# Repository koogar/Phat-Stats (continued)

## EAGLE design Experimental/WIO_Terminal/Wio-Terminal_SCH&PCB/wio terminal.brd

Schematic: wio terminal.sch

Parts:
ANT2: 2.4G+5G; ANT2P-AMEBA-D-MODULE
BUZ1: LET5020CS-03L-4.0-12-R; BZ3-SMD-5.0X5.0X2.5MM
C1, C6: 22uF; C0603
C2, C3: 10uF; C0603
C4: 10uF/10V; C0603
C5, C7, C8, C10, C11, C14, C15, C29, C30, C31, C32, C33, C35, C36, C39, C48: 100nF; C0402
C9, C16, C34, C37, C41, C53, C54, C55: 1uF; C0402
C12, C13, C42, C43: 10pF; C0402
C27, C28: DNP; C0402
C38, C40, C60, C61, C62, C64, C65, C66, C67: 10uF; C0402
C49, C50: 22pF; C0402
C51, C52: 12pF; C0402
C63: 22uF/10V; AVX-A
D1, D6, D8: ESD9B3.3ST5G; ESD-0402
D2, D3, D4: CESDP0402UC5VB; ESD-0402
D5, D9: B5819WS; SOD-323
D7: Blue 90D; LED-SIDE-VIEW-0603-RIGHT
D10: IR; LED-0603
D15: SP3012-06UTG; UDFN14-0.5-3.5X1.35X0.5MM
F1: 1206L300SLTHYR; F1206
FB2, FB3: 120R/2A; F0402
J1: ST-TF-003J; MICRO-SD9+4P-SMD-16.1X14.5X1.85MM
J2: DL; H5-SMD-2.0-TEST
J3: FPC-CONNECTOR-10PTOP''; FPC10-SMD-0.5-10.6X3.5X4.5MM
J4, J5: SMD_GROVE; HW4-SMD-2.0-90D
J6: XW05200-20; FPC20-SMD-0.5-90D
J7: SMD_Header; H6-SMD-2.0_TEST
K1, K2, K3: BUTTON-2+2P-TS-1073B; SW2+2P-3.45-4.8X2.5X1.8MM
L2: 2.2uH; L0805
L3: 0.5pF; L0402
L5: SPH252012H1R2MT; L2520
L6: CBC3225T100MR; L2520
LED1: Green 90D; LED-SIDE-VIEW-0603-RIGHT
MIC1: B4013AM422-042; MIC2-SMD-4X4MM
Q1, Q3, Q4, Q13, Q16: 2N7002,215; SOT-23
Q2, Q7, Q8, Q9, Q10, Q12, Q14, Q15: CJ3407; SOT-23
Q11: BC856S; SOT-363
R1, R2: 5.1K; R0402
R3, R4, R13, R14, R20, R38, R48, R49, R54, R61, R62, R63: 4.7K; R0402
R5, R8, R12, R17, R21, R39, R40, R41, R42, R46, R53, R66, R67, R68, R69, R72, R79, R81, R82, R83: 0R; R0402
R6, R35, R43, R44, R45, R57, R74, R75, R76: 33R; R0402
R7, R16, R18, R19, R23, R24, R36, R37, R84, R85, R86, R87, R91, R95, R100: 100K; R0402
R9, R22, R26, R27, R77, R94, R96, R97, R98: 10K; R0402
R10, R32, R33, R34, R50, R58, R59, R60, R64, R65, R73, R90, R93, R102, R103: DNP; R0402
R11: 4.7k; R0402
R25, R28, R31, R88, R99: 1K; R0402
R29, R52, R78, R80: 100k; R0402
R30: 330R; R0402
R47, R51: 1k; R0402
R55, R56: 22R; R0402
R70: 150K; R0402
R71: 33K; R0402
SW1: DHT-1500; SWITCH-2X3P
SW3: MK-13E03N-G; SW4-SMD-11.2X3.6MM
U1: ATSAMD51P19A; TFBGA120-0.5-8X8MM
U2: LMV358IDGKR; MSOP8-0.65-3X3MM
U3: RPI; H2X20-SMD-2.54-50.8X5MM-LONG
U4: LCD; LCM18-0.8-60.26X42.72X2.2MM
U5: LIS3DHTR; LGA16-0.5-3X3MM
U8: SENSOR-PD15-22C/TR8; SNR4-SMD-3.2X2.7MM
U9: SN74LVC1G125DCKR; SC-70-5
U10: RTL8720D; MODULE-32P-0.8-13X12MM-MOTHER
U11: ATECC608; UDFN8-0.5-2X3X0.5MM
U12: MP2161GJ; TSOT23-8
U13: AP2112K-3.3TRG1; SOT-23-5
U14: W25Q32JVZPIM; SOIC8-1.27-5.3X5.3MM
USB1: USB_TYPE C; USB2.0-TYPE-C
X2: 32.768KHz FC-12M; X2-SMD-L2.0X1.2X0.55MM
X4: 32MHz / 306010026; X4-SMD-3.2X2.5X0.7MM

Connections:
3V3_OUTPUT_CTR: R99.2, U1.P12 (PC15/I15/SERCOM7+6.3/TCC0.5+1.1)
5V_OUTPUT_CTR: R88.1, U1.R11 (PC14/I14/SERCOM7+6.2/TCC0.4+1.0)
A0/D0: J5.1, U1.J2 (PB08/I8/AIN0.2+1.0/SERCOM4.0/TC4.0/PTC), U3.13 (GPIO27/GEN2)
A1/D1: J5.2, U1.K1 (PB09/I9/AIN0.3+1.1/SERCOM4.1/TC4.0/PTC), U3.15 (GPIO22/GEN3)
A2/D2: U1.M1 (PA07/I7/AIN0.7/SERCOM0.1/TC1.1/PTC), U3.16 (GEN4/GPIO23)
A3/D3: U1.F1 (PB04/I4/AIN1.6/PTC), U3.18 (GEN5/GPIO24)
A4/D4: U1.G1 (PB05/I5/AIN1/7/PTC), U3.22 (GEN6/GPIO25)
A5/D5: U1.H2 (PB06/I6/AIN1.8/PTC), U3.32 (GPIO12)
A6/D6: U1.K2 (PA04/I4/VREFB/AIN0.4/SERCOM0.1/TC0.0/PTC), U3.33 (GPIO13)
A7/D7: U1.J1 (PB07/I7/AIN1.9/PTC), U3.36 (GPIO16)
A8/D8: U1.L2 (PA06/I6/VREFC/AIN0.6/SERCOM0.1/TC1.0/PTC), U3.37 (GPIO26)
BUTTON1: K1.2, R49.1, U1.A10 (PC26/I10/TRACEDATA.1)
BUTTON2: K2.2, R3.1, U1.A9 (PC27/I11/SERCOM1.0/TRACECLK)
BUTTON3: K3.2, R4.1, U1.B9 (PC28/I12/SERCOM1.1/TRACEDATA.0)
BUZZER_CTR: R5.1, U1.P9 (PD11/I6/SERCOM7+6.3/TCC0.4)
DAC0: U1.E1 (PA02/I2/AIN0.0/VOUT0), U3.11 (GPIO17/GEN0)
DAC1: U1.L1 (PA05/I5/AIN0.5/VOUT1/SERCOM0.2/TC0.1), U3.26 (!CE!/GPIO7)
DN: D3.1, R55.1, USB1.A7 (A7/DN1), USB1.B7 (B7/DN2)
DP: D4.1, R56.2, USB1.A6 (A6/DP1), USB1.B6 (B6/DP2)
FPC_D3/PWM3: J6.4, U1.A12 (PB28/I14/SEROM2+4.2/TCC1.4/I2SSCK.1)
FPC_D4/PWM4: J6.5, U1.G15 (PB17/SERCOM5.1/I2SMCK0/TC6.1+TCC3.1+0.5)
FPC_D5/PWM5: J6.6, U1.B11 (PB29/I15/SERCOM2+4.3/TCC1.5/I2SMCK.1)
FPC_D6/PWM6: J6.7, U1.R13 (PA14/I14/SERCOM2+4.2/TC3.0+TCC2.0+1.2)
FPC_D7/A7: J6.8, U1.C2 (PC01/I1/ADC1.11)
FPC_D8/A8: J6.9, U1.D1 (PC02/I2/ADC1.4)
FPC_D9/A9: J6.10, U1.E2 (PC03/I3/ADC1.5)
FPC_D10/PWM10: J6.11, U1.N1 (PC04/I4/SERCOM6.0/TCC0.0)
FPC_D11/A11: J6.12, U1.B4 (PC31/I15/AIN1.13)
FPC_D12/A12: J6.13, U1.G2 (PD00/I0/AIN1.14)
FPC_D13/A13: R79.2, U1.H1 (PD01/I1/AIN1.14)
GND: ANT2.1, C1.1, C2.1, C3.1, C4.1, C5.1, C6.1, C7.2, C8.2, C9.2, C10.2, C11.1, C12.2, C13.2, C14.1, C15.2, C16.2, C27.1, C28.1, C29.1, C30.1, C31.1, C32.2, C33.2, C35.2, C36.2, C37.2, C38.2, C39.2, C40.2, C41.2, C42.2, C43.2, C48.2, C49.1, C50.1, C51.2, C52.2, C53.2, C54.2, C60.2, C61.2, C62.2, C63.-, C64.1, C65.1, C66.1, C67.1, D1.1, D2.2, D3.2, D4.2, D6.1, D8.1, D15.5 (10), D15.10, J1.6 (VSS), J1.G1, J1.G2, J1.G3, J1.G4 (G3), J2.2, J3.6, J3.P1, J3.P2, J4.4, J5.4, J6.17, J6.18, J6.P1, J6.P2, J7.5, K1.1, K1.3 (S1), K1.4 (S2), K2.1, K2.3 (S1), K2.4 (S2), K3.1, K3.3 (S1), K3.4 (S2), LED1.2 (-), MIC1.2 (-), MIC1.3 (-), MIC1.4 (-), MIC1.5 (-), Q1.2 (S), Q3.2 (S), Q4.2 (S), Q13.2 (S), Q16.2 (S), R1.1, R2.1, R7.1, R16.2, R19.2, R23.2, R25.1, R28.1, R50.2, R52.1, R54.2, R72.1, R77.1, R78.1, R80.2, R91.2, R93.1, R95.1, R97.1, R98.1, R100.1, SW1.5, SW1.7, SW1.8, SW3.3, U1.D2 (GNDIO0), U1.F6 (GNDIO7), U1.F9 (GNDIO6), U1.G10 (GNDIO5), U1.H6 (GNDANA0), U1.J6 (GNDIO1), U1.J10 (GNDIO4), U1.K8 (GNDIO2)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
GPCLK0: U1.R5 (PB14/I14/SERCOM4.2/PCC8/TC5.0+TCC4.0+0.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), U3.7 (GPIO4/GCKL)
GPCLK1: U1.R4 (PB12/I12/SERCOM4.0/I2SCK1/TC4.0+TCC3.0+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), U3.29 (GPIO5)
GPCLK2: U1.P6 (PB13/I13/SERCOM4.1/I2SMCK1/TC4.1+TCC3.1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), U3.31 (GPIO6)
GYROSCOPE_INT1: U1.K14 (PC21/I5/TCC0.5/SDHC1.SDWP), U5.11 (INT1)
I2C0_SCL: R13.2, U1.R12 (PA12/I12/I2C/SERCOM2.0+4.1/TC2.0+TCC0.7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), U3.28 (ID_SC), U5.4 (SCL/SPC), U11.6 (SCL)
I2C0_SDA: R14.2, U1.P13 (PA13/I13/I2C/SERCOM2.1+4.0/TC2.1+TCC0.7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), U3.27 (ID_SD), U5.6 (SDA/SDI/SDO), U11.5 (SDA)
I2C1_SCL: J4.1, R33.1, U1.R15 (PA16/I2C/I0/SERCOM1.0+3.1/TC2.0+TCC1.0+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), U3.5 (GPIO3/SCL1)
I2C1_SDA: J4.2, R34.1, U1.P14 (PA17/I2C/I1/SERCOM1.1+3.0/TC2.1+TCC1.1+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), U3.3 (GPIO2/SDA1)
I2S_BLCK: U1.H15 (PB16/I0/SERCOM5.0/I2SCK0/TC6.0+TCC3.0+0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), U3.12 (GPIO18)
I2S_LRCLK: U1.E14 (PA20/I4/SERCOM3+5.2/I2SFS0/TC7.0+TCC1.4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), U3.35 (GPIO19)
I2S_SDIN: U1.D15 (PA21/I5/SERCOM3+5.3/I2SDO/TC7.1+TCC1.5+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), U3.38 (GPIO20)
I2S_SDOUT: U1.D14 (PA22/I2C/16/SERCOM3.0+5.1/I2SDI/TC4.0+T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), U3.40 (GPIO21)
IRQ0: R103.1, U1.L15 (PC20/I4/TCC0.4/SDHC1.SDCD), U10.2
IR_CTL: R47.2, U1.B5 (PB31/I15/SERCOM5.0/TC0.1+TCC4.1+0.7)
LCDVCC_3V3: C29.2, C30.2, C31.2, FB2.2, R48.2, U4.9 (VCC), U4.10 (LEDA)
LCD_BACKLIGHT_CTR: R17.2, U1.N2 (PC05/I5/SERCOM6.0)
LCD_CS: R74.2, U1.E15 (PB21/SERCOM3.1+7.0/TCC1.3)
LCD_D/C: R57.2, U1.P1 (PC06/I6/SERCOM6.2/SDHC0.SDCD)
LCD_MISO: R76.2, U1.G14 (PB18/I2/SERCOM5+7.2/TCC1.0+QDI.0)
LCD_MOSI: R75.2, U1.F15 (PB19/I3/SERCOM5+7.3/CC1.1/QDI.1)
LCD_RESET: R48.1, U1.P2 (PC07/I9/SERCOM6.3/SDHC0.SDWP), U4.2 (RESET)
LCD_SCK: R35.2, U1.F14 (PB20/I4/SERCOM3.0+7.1/TCC1.2/QDI.2)
LCD_XL: R39.1, U1.P10 (PC10/I10/SERCOM6.2+7.2/TCC0.0+1.4)
LCD_XR: R41.1, U1.R10 (PC12/I12/SERCOM7.0+6.1/TCC0.2+1.6)
LCD_YD: R42.1, U1.P11 (PC13/I13/SERCOM7.1+6.0/TCC0.3+1.7)
LCD_YU: R40.1, U1.R9 (PC11/I11/SERCOM6+7.3/TCC0.1+1.5)
MCU_FLASH_QSPI_CLK: U1.R3 (PB10/I10/SERCOM4.2/I2SDI/TC5.0+TCC0.4+1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), U14.6 (CLK)
MCU_FLASH_QSPI_CS: R32.1, U1.P5 (PB11/I11/SERCOM4.3/I2SFS1/TC5.1+TCC0.5+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), U14.1 (/CS)
MCU_FLASH_QSPI_IO0: U1.R1 (PA08/I2C/AIN0.8+1.2/SERCOM0.0+2.1/I2SMC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), U14.5 (DIO)
MCU_FLASH_QSPI_IO1: U1.P3 (PA09/I2C/I9/AIN0.9+1.3/SERCOM0.1+2.0/I2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), U14.2 (DO)
MCU_FLASH_QSPI_IO2: R58.1, U1.R2 (PA10/I10/AIN0.10/SERCOM0+2.2/I2SCK1/TC1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), U14.3 (/WP)
MCU_FLASH_QSPI_IO3: R59.1, U1.P4 (PA11/I11/AIN0.11/SERCOM0+2.3/I2SDO/TC1.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), U14.7 (/HOLD)
MCU_RESET: D6.2, J3.4, J7.4, R30.2, SW3.1, U1.A8 (!RESET)
MIC_OUTPUT: C55.2, U1.A4 (PC30/I14/AIN1.12)
unnamed: L6.1, U1.A6 (VSW)
unnamed: R12.2, U1.F2 (PA03/I3/VREFA/AIN0.1)
unnamed: D2.1, F1.1, USB1.A4_B9 (A4/B9/VBUS), USB1.B4_A9 (B4/A9/VBUS)
unnamed: R1.2, USB1.A5 (A5/CC1)
unnamed: R2.2, USB1.B5 (B5/CC2)
unnamed: Q4.3 (D), R6.2
unnamed: BUZ1.-, D5.+, R6.1
unnamed: Q4.1 (G), R5.2, R7.2
unnamed: C12.1, R35.1, U4.3 (SCL)
unnamed: ANT2.2, C28.2, L3.1
unnamed: R69.1, U1.K15 (PC22/I6/SERCOM1.0+3.1/TCC0.6)
unnamed: R68.1, U1.J14 (PC23/I7/SERCOM1.1+3.0/TCC0.7)
unnamed: Q7.1 (G), Q8.3 (D), R91.1, SW3.2
unnamed: C13.1, R57.1, U4.4 (D/C)
unnamed: R65.2, U10.23
unnamed: R74.1, U4.5 (CS)
unnamed: C43.1, R75.1, U4.6 (SDA)
unnamed: R10.2, U10.22
unnamed: Q13.3 (D), R83.2
unnamed: Q13.1 (G), R47.1, R80.1
unnamed: C42.1, R76.1, U4.7 (SDO)
unnamed: Q9.1 (G), Q14.1 (G), Q16.3 (D), R93.2, R94.1
unnamed: R66.1, U10.7
unnamed: R67.1, U10.10
unnamed: R46.1, U4.11 (LEDK), U4.12 (LEDK), U4.13 (LEDK), U4.14 (LEDK)
unnamed: Q2.1 (G), R19.1, R20.2, U9.4 (Y)
unnamed: Q1.1 (G), R16.1, R17.1
unnamed: C34.2, R23.1, R24.2
unnamed: R18.2, R21.1, U9.1 (!OE!), U9.2 (A)
unnamed: LED1.1 (+), R31.2
unnamed: R24.1, U2.3 (+IN1)
unnamed: C4.2, C5.2, F1.2, Q2.3 (D)
unnamed: C34.1, MIC1.1 (+), R22.2
unnamed: R25.2, R26.1, U2.2 (-IN1)
unnamed: R26.2, U2.1 (OUT1), U2.5 (+IN2)
unnamed: R27.1, R28.2, U2.6 (-IN2)
unnamed: C50.2, U1.B1 (PA01/I1/SERCOM1.1/TC2.1), X2.1
unnamed: C36.1, C37.1, C38.1, L6.2, U1.A7 (VDDCORE)
unnamed: R39.2, U4.15 (XL)
unnamed: C49.2, U1.A1 (PA00/I0/SERCOM1.0/TC2.0), X2.2
unnamed: C35.1, R9.1, R30.1
unnamed: R40.2, U4.16 (YU)
unnamed: Q11.2 (B), Q11.5 (B), Q11.6 (C), R98.2
unnamed: R41.2, U4.17 (XR)
unnamed: R42.2, U4.18 (YD)
unnamed: R81.1, U10.9
unnamed: Q1.3 (D), R46.2
unnamed: R82.1, U10.8
unnamed: R77.2, R79.1, U8.2-1 (2), U8.2-2 (2)
unnamed: Q10.1 (G), Q11.3 (C), R97.2
unnamed: D10.-, R83.1
unnamed: Q8.1 (G), R29.1, SW3.4
unnamed: Q9.3 (D), Q14.3 (D)
unnamed: C52.1, R8.2, X4.1 (X1)
unnamed: R50.1, U1.C1 (PC00/I1/ADC1.10)
unnamed: D7.2 (-), Q3.3 (D)
unnamed: D7.1 (+), R51.2
unnamed: Q3.1 (G), R52.2, R53.2
unnamed: D15.1 (14), D15.14, J1.8 (DATA1), R60.1
unnamed: Q12.3 (D), Q15.3 (D)
unnamed: Q16.1 (G), R88.2, R100.2
unnamed: C55.1, R27.2, U2.7 (OUT2)
unnamed: Q12.1 (G), Q15.1 (G), R95.2, R96.1, R99.1
unnamed: L5.1, U12.3 (SW)
unnamed: D15.7 (8), D15.8, J1.1 (DATA2), R64.1
unnamed: R71.1, R72.2
unnamed: C27.2, L3.2, U10.31
unnamed: R70.1, R71.2, U12.7 (FB)
unnamed: D15.2 (13), D15.13, J1.7 (DO), R43.1
unnamed: D15.3 (12), D15.12, J1.5 (SCLK), R44.1
unnamed: D15.4 (11), D15.11, J1.3 (DI), R45.1
PWR_EN: Q7.3 (D), R73.1, R78.2, R90.2, U12.8 (EN), U13.3 (!SHUTDOWN)
RPI_3V3: Q10.3 (D), Q11.1 (E), Q15.2 (S), U3.1 (3V3), U3.17 (3V3)
RPI_5V: D9.+, Q14.2 (S), R20.1, U3.2 (5V0), U3.4 (5V0)
RTL8720D_CHIP_PU: C9.1, J2.5, J3.10, R11.1, U1.P15 (PA18/I2/SERCOM1+3.2/TC3.0+TCC1.2+0.6/PTC), U10.24
RTL8720D_HSPI_CLK: R10.1, R66.2, U1.B13 (PB25/SERCOM0.1+2.0/QDI.2)
RTL8720D_HSPI_CS: R82.2, U1.B10 (PC25/I9/SERCOM0+2.3/TRACEDATA.2)
RTL8720D_HSPI_MISO: R81.2, U1.A11 (PC24/I8/SERCOM0+2.2/TRACEDATA.3)
RTL8720D_HSPI_MOSI: R65.1, R67.2, U1.B14 (PB24/I8/SERCOM0.0+2.1/QDI.1)
RTL8720D_RXD: J2.4, J3.9, R69.2, U10.26
RTL8720D_TXD: J2.3, J3.8, R68.2, U10.25
RXD: U1.B12 (PB27/I13/SERCOM2.1+4.0/TCC1.3), U3.10 (RXD0/GPIO15)
SD_CS: D15.6 (9), D15.9, J1.2 (CS), R63.1, U1.L14 (PC19/I3/SERCOM6+0.3/TCC0.3)
SD_DET: D8.2, J1.9 (CDN), R36.1, U1.H14 (PD21/I11/SERCOM1+3.3/TCC1.1/SDHC1.SDWP)
SD_MISO: R43.2, R61.1, U1.M15 (PC18/I2/SERCOM6.2+0.2/TCC0.2/QDI.2)
SD_MOSI: R45.2, R62.1, U1.N15 (PC16/I0/SERCOM6.0+0.1/TCC0/QDI.0)
SD_SCK: R44.2, U1.M14 (PC17/I1/SERCOM6.1+0.0/TCC0.1/QDI.1)
SPI_CS: U1.B3 (PB01/I1/AIN0.13/SERCOM5.3/TC7.1/PTC), U3.24 (!CE0!/GPIO8)
SPI_MISO: J6.2, U1.A3 (PB00/I0/AIN0.12/SERCOM5.2/TC7.0/PTC), U3.21 (GPIO9/MISO)
SPI_MOSI: J6.1, U1.A2 (PB02/I2/AIN0.14/SERCOM5.0/TC6.0+TCC2.2/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), U3.19 (GPIO10/MOSI)
SPI_SCK: J6.3, U1.B2 (PB03/I3/AIN0.15/SERCOM5.1/TC6.1/PTC), U3.23 (GPIO11/SCLK)
SWDCLK: J3.1, J7.1, R33.2, R38.2, U1.B7 (PA30/I14/SERCOM1.2/SWCLK)
SWDIO: J3.2, J7.2, R34.2, R54.1, U1.B6 (PA31/I15/SERCOM1.3/SWDIO)
SWITCH_B: R86.1, SW1.4, U1.R8 (PD12/I7/TCC0.5)
SWITCH_U: R87.1, SW1.6, U1.J15 (PD20/I10/SERCOM1+3.2/TCC1.0/SDHC1.SDCD)
SWITCH_X: R37.1, SW1.1, U1.R6 (PD08/I3/SERCOM7.0+6.1/TCC0.1)
SWITCH_Y: R85.1, SW1.3, U1.P8 (PD09/I4/SERCOM7.1+6.0/TCC0.2)
SWITCH_Z: R84.1, SW1.2, U1.R7 (PD10/I5/SERCOM7+6.2/TCC0.3)
SWO: J3.3, J7.3, U1.A5 (PB30/I14/SERCOM5.1/TC0.0+TCC4.0+0.6/SWO)
SYNC: R102.1, U1.N14 (PA19/I3/SERCOM1+3.3/TC3.1+TCC1.3+0.7/PT), U10.3
TXD: U1.A13 (PB26/I12/SERCOM2.0+4.1/TCC1.3), U3.8 (TXD0/GPIO14)
USB_5V: C3.2, C8.1, C66.2, C67.2, D9.-, J6.19, J6.20, Q2.2 (S), Q7.2 (S), Q8.2 (S), Q9.2 (S), R29.2, R73.2, R90.1, R94.2, U12.2 (VIN), U13.1 (VIN)
USB_D+: R56.1, U1.B15 (PA25/19/SERCOM3+5.3/D+)
USB_D-: R55.2, U1.C15 (PA24/I8/SERCOM3+5.2/D-)
USB_HOST_EN: R21.2, U1.B8 (PA27/I11)
USER_LED: R53.1, U1.R14 (PA15/I15/SERCOM2+4.3/TC3.1+TCC2.1+1.3)
VCC3V3_8720: C1.2, C2.2, C6.2, C7.1, C10.1, J2.1, R11.2, R102.2, R103.2, U10.16, U13.5 (VOUT)
VCC3V3_MCU_A: C33.1, C60.1, L2.1, R12.1, R22.1, U1.G6 (VDDANA0), U1.M2 (VDDANA1), U2.8 (+V)
VCC3V3_MCU_D: C15.1, C16.1, C39.1, C40.1, C41.1, C48.1, C62.1, D1.2, FB3.2, J1.4 (VDD), J7.6, R3.2, R4.2, R9.2, R32.2, R36.2, R37.2, R38.1, R49.2, R51.1, R58.2, R59.2, R60.2, R61.2, R62.2, R63.2, R64.2, R84.2, R85.2, R86.2, R87.2, U1.F7 (VDDIO7), U1.F8 (VDDIO6), U1.F10 (VDDIO5), U1.H10 (VDDIO4), U1.K6 (VDDIOB1), U1.K7 (VDDIOB2), U1.K10 (VDDIO3), U14.8 (VCC)
VCC_3V3: BUZ1.+, C11.2, C14.2, C32.1, C53.1, C54.1, C61.1, C63.+, C64.2, C65.2, D5.-, D10.+, FB2.1, FB3.1, J4.3, J5.3, J6.15, J6.16, L2.2, L5.2, Q10.2 (S), Q11.4 (E), Q12.2 (S), R13.1, R14.1, R18.1, R31.1, R70.2, R96.2, U5.1 (VDD_IO), U5.8 (CS), U5.14 (VDD), U8.1-1 (1), U8.1-2 (1), U9.5 (VCC), U11.8 (VCC), U12.5 (OUT)
XIN: R8.1, U1.A15 (PB22/I6/SERCOM1+5.2/TC7.0/QDI.2)
XOUT: C51.1, U1.A14 (PB23/I7/SERCOM1+5.3/TC7.1/QDI.0), X4.3 (X2)

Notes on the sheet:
First version
20190812
Milo
Power
ATSAMD51P19A
Buzzer & MIC
WIFI+BLE
Gyroscope & LCD
8720 module Download
Replace with 0R resistance
USB HOST selection Power selection
Close to USB TYPE C
Close to ATSAMD51P19A power Pin
Header Interface and Button
Input current:2A
Output current:2A
Input current 500mA
Input current 600mA
ATSAMD51P19A Download
I2C Address 0x19
To guarantee the XOSC32K behavior in crystal mode,PC00 must be static
MCU Reset
Power ON
Power OFF
PA28/CTS/PWM6/RREF
PB17/SPI_DATA1
PB16/SPI_CS
PB13/SPI_CLK
PB14/SPI_DATA0
ADC6
ADC4/TXD
ADC5/RXD/I2C_SDA
PA25/RXD/USB_DM/I2C_SCL
PA26/TXD/USB_DP
PA30/PWM7/SWD_CLK
PA27/RTS/SWD_DATA
PB20/TXD/PWM12/I2S_CLK/SPI_DATA0/I2C_SCL
PB21/RXD/PWM13/I2S_WS/SPI_CLK/I2C_SDA
PA15/CTS/CS
PA14/RTS/CLK/I2S_TX2

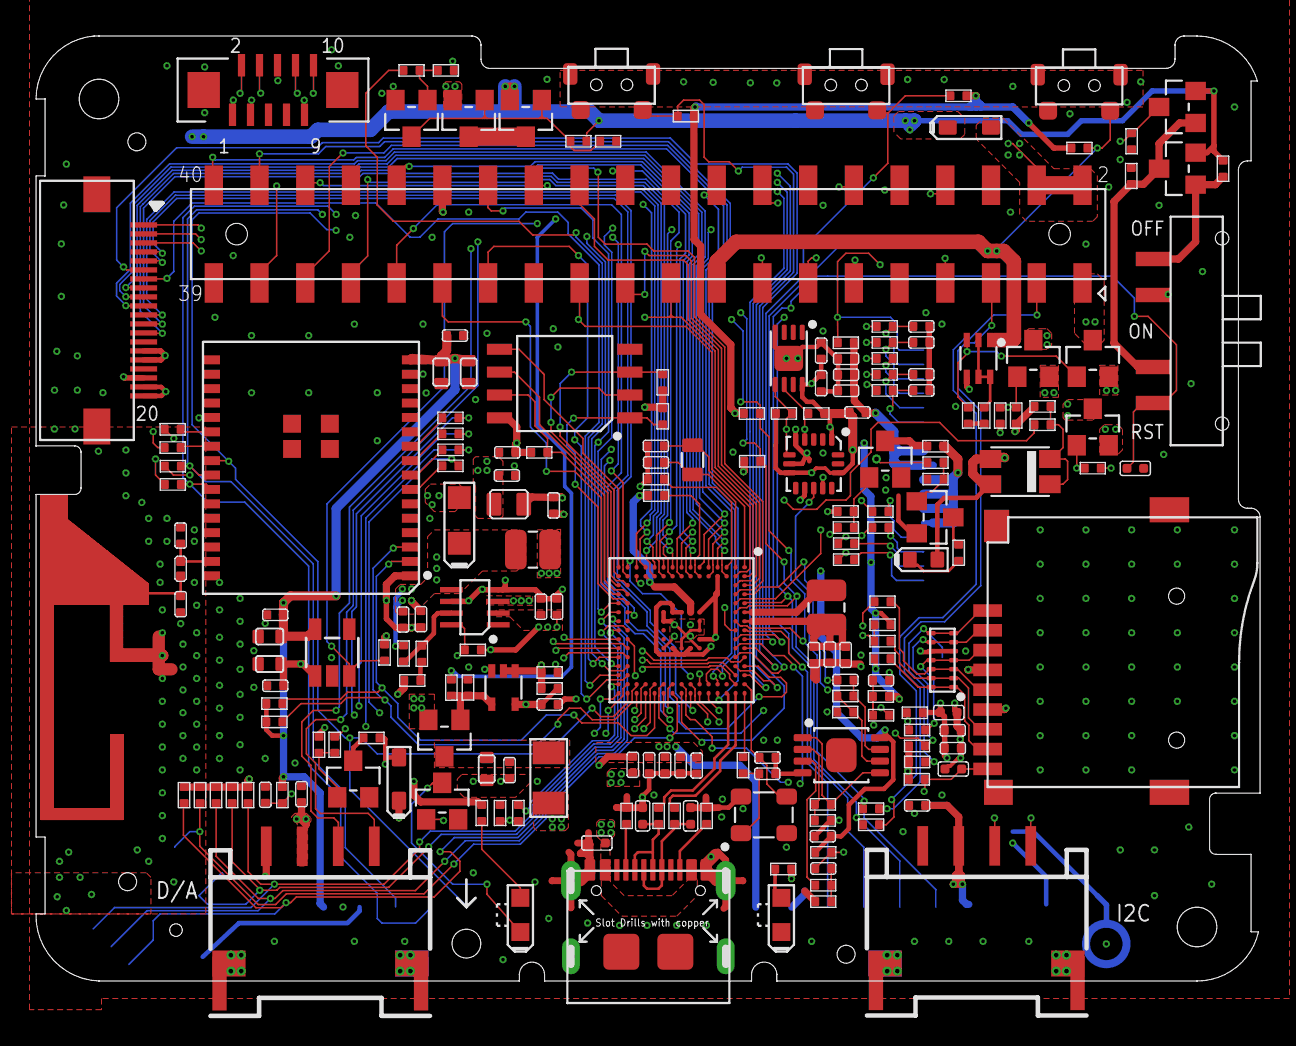
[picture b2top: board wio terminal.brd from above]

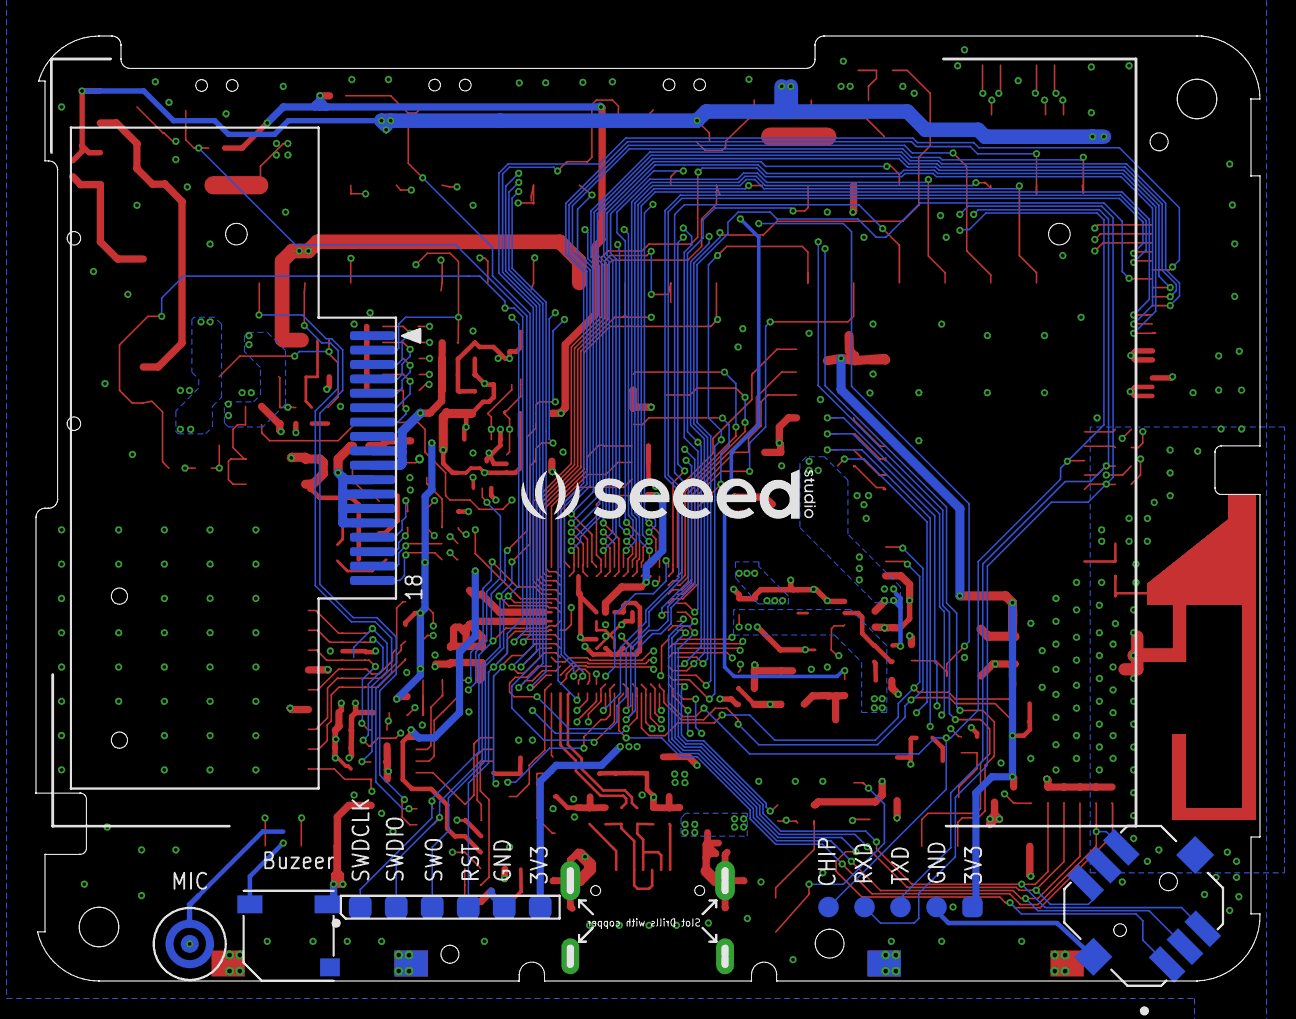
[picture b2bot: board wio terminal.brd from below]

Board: 4 copper layers, 68.0 x 52.5 mm, 212 parts (8 on the bottom side), 177 nets.

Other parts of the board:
U$2: LOGO-SEEED-VECTOR; SEEED-SILK-VECTOR

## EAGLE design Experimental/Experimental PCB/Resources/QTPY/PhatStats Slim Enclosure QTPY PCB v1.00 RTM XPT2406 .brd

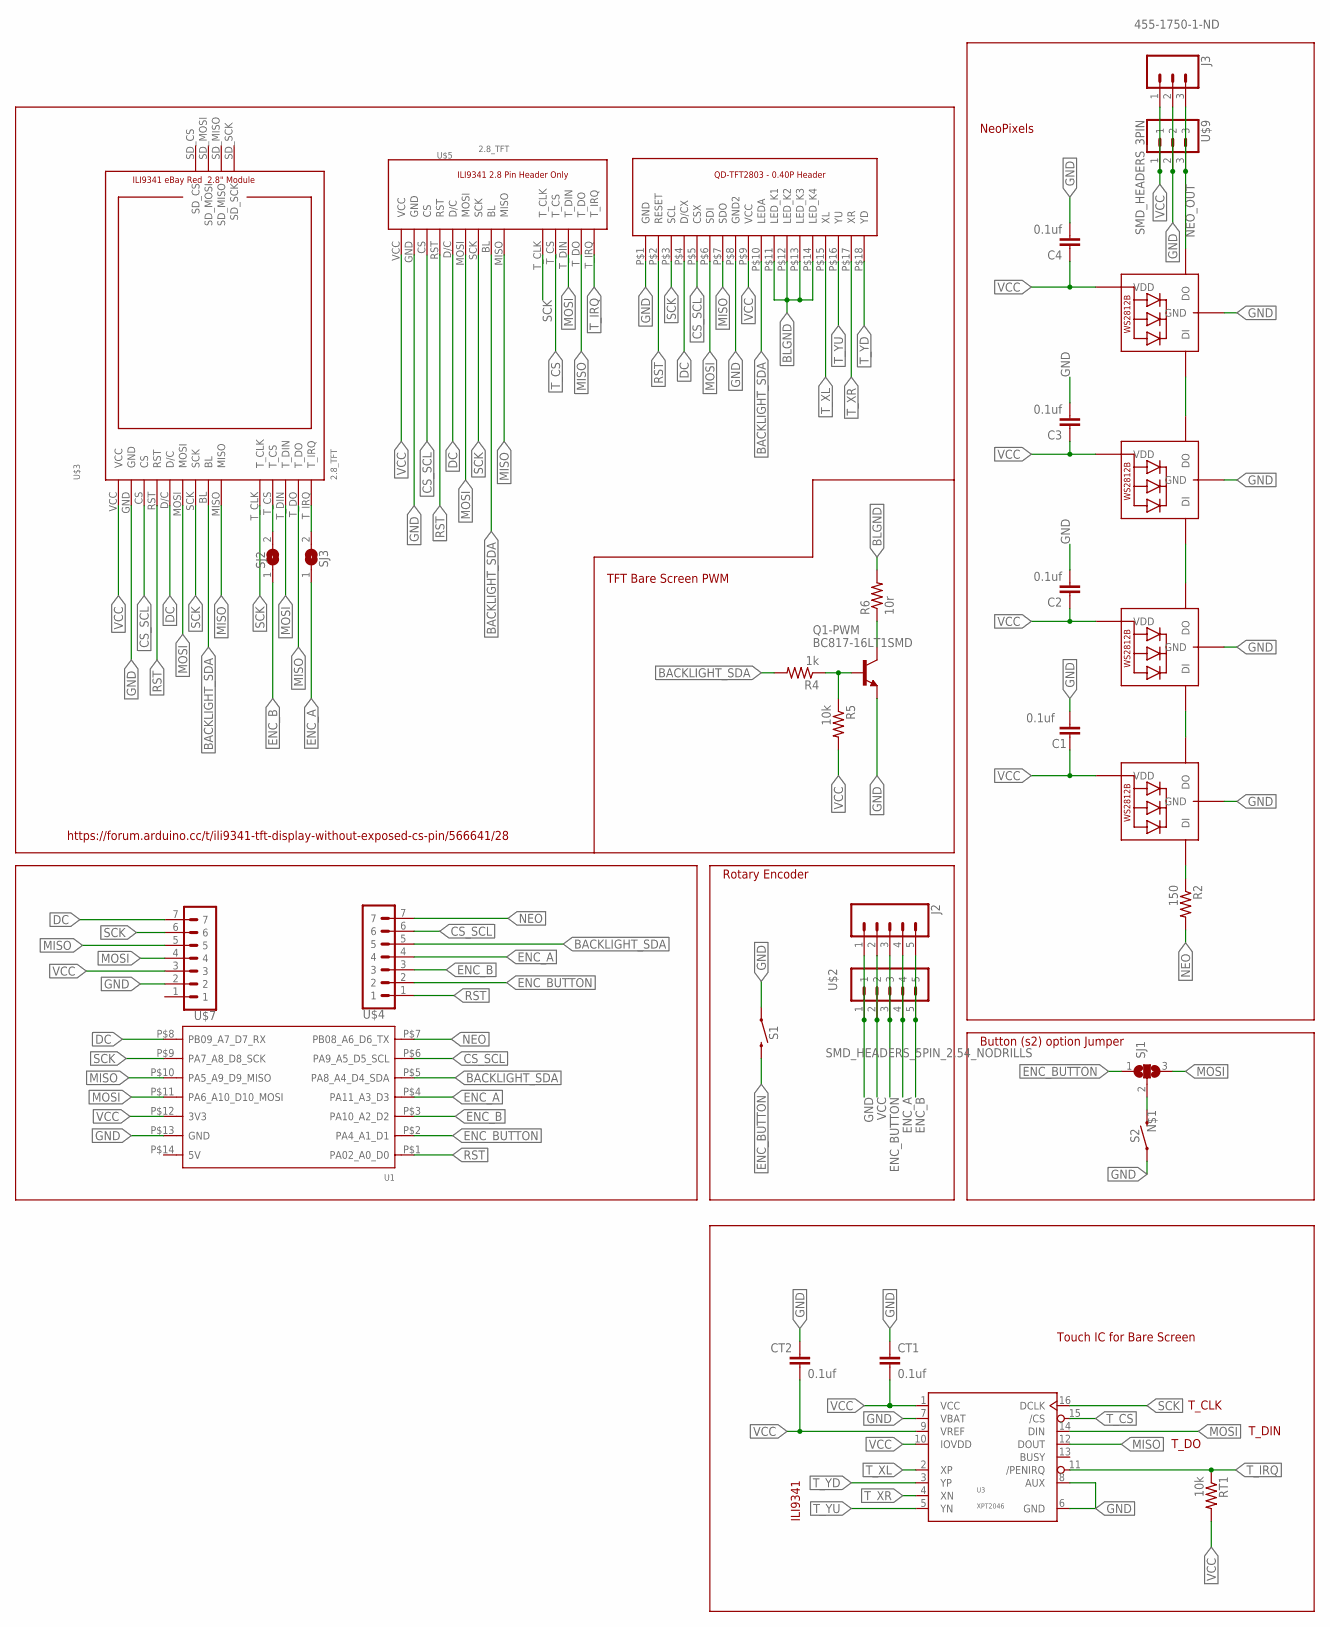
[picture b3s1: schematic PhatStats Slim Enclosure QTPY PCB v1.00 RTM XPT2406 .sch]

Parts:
0: ILI9341-2.8
C1, C2, C3, C4: 0.1uf; C1206
CT1, CT2: 0.1uf; C1206
J2: CONN_05; 1X05
J3: 455-1750-1-ND; 1X03
NEO1, NEO2, NEO3, NEO4: WS2812B5050; WS2812B
Q1-PWM: BC817-16LT1SMD; SOT23-BEC
R2: 150; M1206
R4: 1k; M1206
R5: 10k; M1206
R6: 10r; M1206
RT1: 10k; M1206
S1, S2: MOMENTARY-SWITCH-SPST-SMD-6.2MM-TALL; TACTILE_SWITCH_SMD_6.2MM_TALL
SJ1: SJ2W; SJ_2
SJ2, SJ3: SJ
U1: MOUDLE-SEEEDUINO-XIAO; MOUDLE14P-2.54-21X17.8MM
U3: XPT2046; TSSOP-16
U$2: SMD_HEADERS_5PIN_2.54_NODRILLS; SMD_HEADERS_5PIN
U$3, U$5: 2.8_TFT
U$4, U$7: SMD_HEADERS_7PIN_2.54_NODRILLS; SMD_HEADERS_7PIN
U$9: SMD_HEADERS_3PIN

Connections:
BACKLIGHT_SDA: 0.P$10 (LEDA), R4.2, U1.P$5 (PA8_A4_D4_SDA), U$3.BL, U$4.5, U$5.BL
BLGND: 0.P$11 (LED_K1), 0.P$12 (LED_K2), 0.P$13 (LED_K3), 0.P$14 (LED_K4), R6.2
CS_SCL: 0.P$5 (CSX), U1.P$6 (PA9_A5_D5_SCL), U$3.CS, U$4.6, U$5.CS
DC: 0.P$4 (D/CX), U1.P$8 (PB09_A7_D7_RX), U$3.D/C, U$5.D/C, U$7.7
ENC_A: J2.4, SJ3.1, U1.P$4 (PA11_A3_D3), U$2.4, U$4.4
ENC_B: J2.5, SJ2.1, U1.P$3 (PA10_A2_D2), U$2.5, U$4.3
ENC_BUTTON: J2.3, S1.B2 (2), SJ1.1, U1.P$2 (PA4_A1_D1), U$2.3, U$4.2
GND: 0.P$1 (GND), 0.P$8 (GND2), C1.1, C2.2, C3.2, C4.2, CT1.1, CT2.1, J2.1, J3.2, NEO1.3-GND (GND), NEO2.3-GND (GND), NEO3.3-GND (GND), NEO4.3-GND (GND), Q1-PWM.E, S1.A2 (1), S2.A2 (1), U1.P$13 (GND), U3.6 (GND), U3.7 (VBAT), U3.8 (AUX), U$2.1, U$3.GND, U$5.GND, U$7.2, U$9.2
MISO: 0.P$7 (SDO), U1.P$10 (PA5_A9_D9_MISO), U3.12 (DOUT), U$3.MISO, U$3.T_DO, U$5.MISO, U$5.T_DO, U$7.5
MOSI: 0.P$6 (SDI), SJ1.3, U1.P$11 (PA6_A10_D10_MOSI), U3.14 (DIN), U$3.MOSI, U$3.T_DIN, U$5.MOSI, U$5.T_DIN, U$7.4
unnamed: S2.B2 (2), SJ1.2
unnamed: Q1-PWM.B, R4.1, R5.1
unnamed: NEO2.2-DOUT (DO), NEO3.4-DIN (DI)
unnamed: NEO1.4-DIN (DI), R2.1
unnamed: NEO3.2-DOUT (DO), NEO4.4-DIN (DI)
unnamed: Q1-PWM.C, R6.1
NEO: R2.2, U1.P$7 (PB08_A6_D6_TX), U$4.7
NEODATA: NEO1.2-DOUT (DO), NEO2.4-DIN (DI)
NEO_OUT: J3.3, NEO4.2-DOUT (DO), U$9.3
RST: 0.P$2 (RESET), U1.P$1 (PA02_A0_D0), U$3.RST, U$4.1, U$5.RST
SCK: 0.P$3 (SCL), U1.P$9 (PA7_A8_D8_SCK), U3.16 (DCLK), U$3.SCK, U$3.T_CLK, U$5.SCK, U$5.T_CLK, U$7.6
T_CS: SJ2.2, U3.15 (/CS), U$3.T_CS, U$5.T_CS
T_IRQ: RT1.1, SJ3.2, U3.11 (/PENIRQ), U$3.T_IRQ, U$5.T_IRQ
T_XL: 0.P$15 (XL), U3.2 (XP)
T_XR: 0.P$17 (XR), U3.4 (XN)
T_YD: 0.P$18 (YD), U3.3 (YP)
T_YU: 0.P$16 (YU), U3.5 (YN)
VCC: 0.P$9 (VCC), C1.2, C2.1, C3.1, C4.1, CT1.2, CT2.2, J2.2, J3.1, NEO1.1-VDD (VDD), NEO2.1-VDD (VDD), NEO3.1-VDD (VDD), NEO4.1-VDD (VDD), R5.2, RT1.2, U1.P$12 (3V3), U3.1 (VCC), U3.9 (VREF), U3.10 (IOVDD), U$2.2, U$3.VCC, U$5.VCC, U$7.3, U$9.1

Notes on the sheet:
https://forum.arduino.cc/t/ili9341-tft-display-without-exposed-cs-pin/566641/28
Button (s2) option Jumper
Rotary Encoder
TFT Bare Screen PWM
NeoPixels
ILI9341
T_CLK
T_DIN
T_DO
Touch IC for Bare Screen

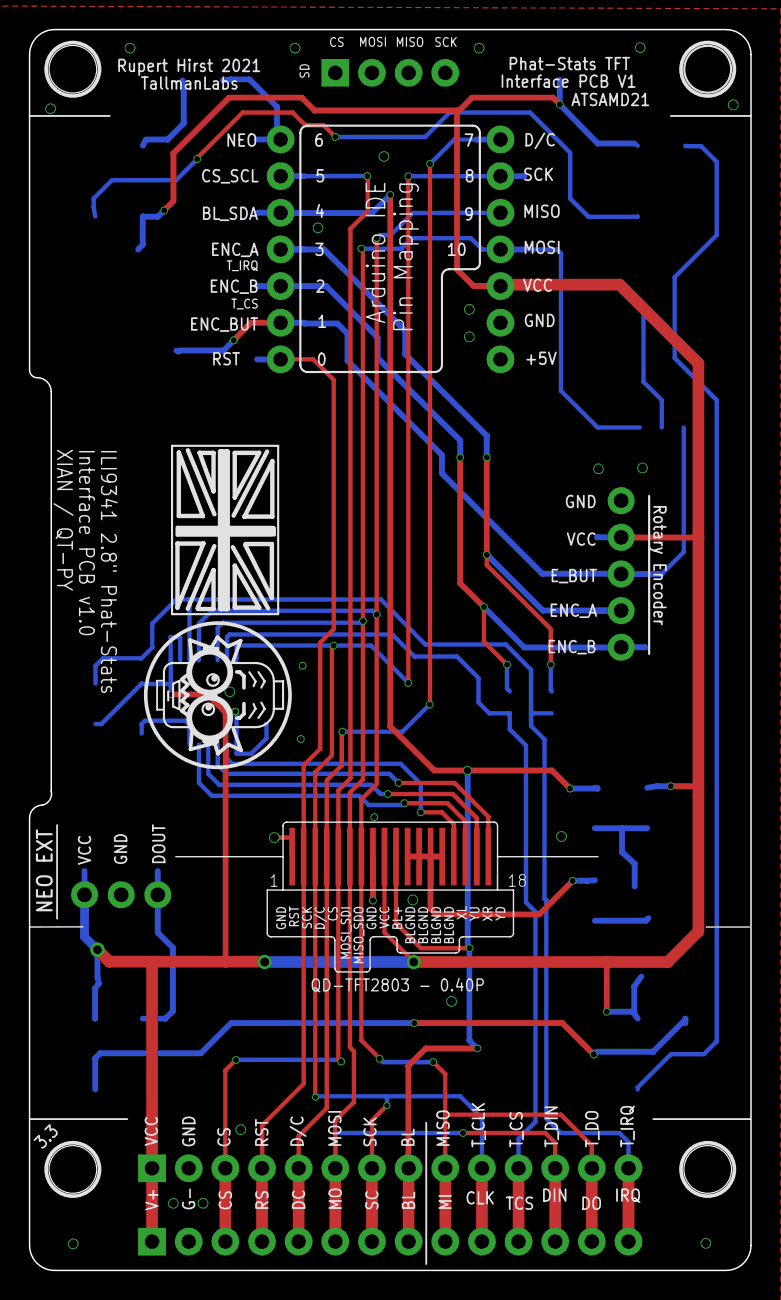
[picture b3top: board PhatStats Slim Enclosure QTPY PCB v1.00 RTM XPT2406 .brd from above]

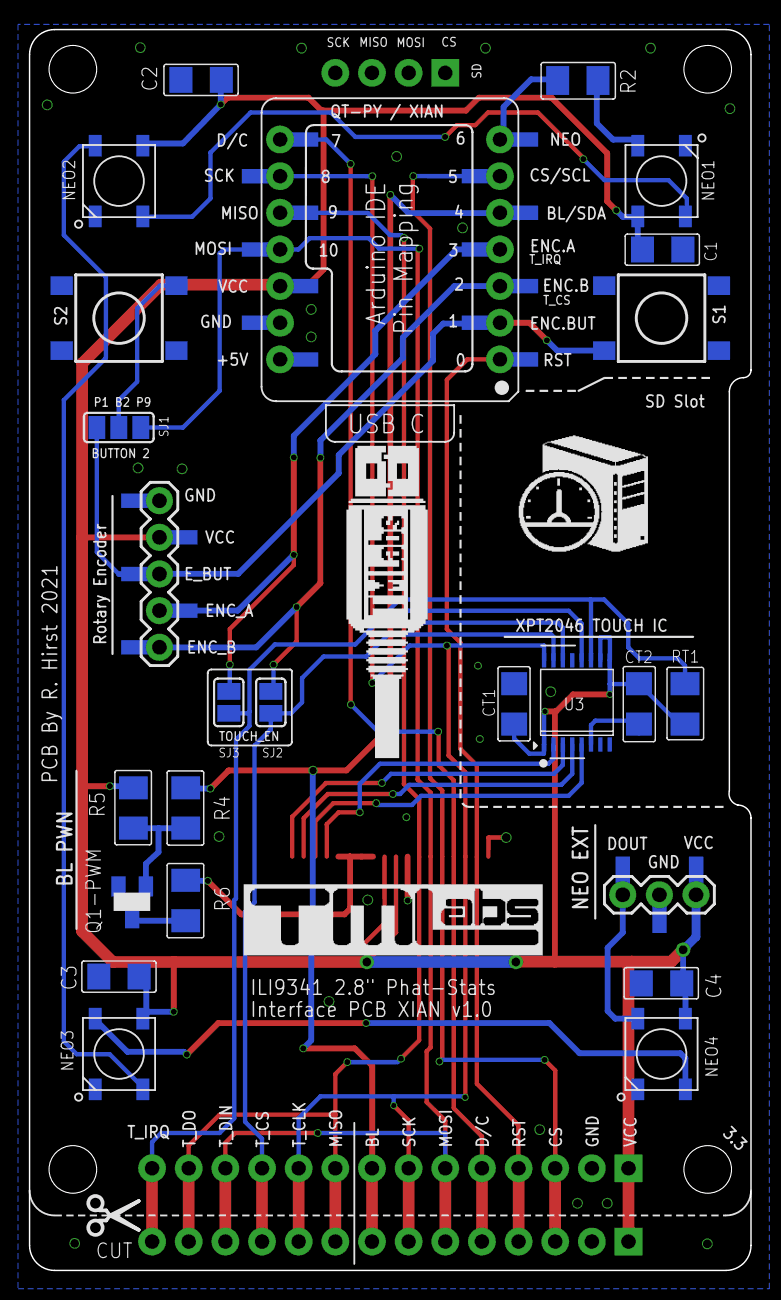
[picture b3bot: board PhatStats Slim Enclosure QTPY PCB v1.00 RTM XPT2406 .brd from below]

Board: 2 copper layers, 50.0 x 86.0 mm, 37 parts (33 on the bottom side), 28 nets.

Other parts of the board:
U$1: TMSLOGO_PROF_UNION_LRG
U$6: HSMSMALL
U$8: TMLUSBMEDIUM
U$10: SCISSORS_TS
U$14: TMSLOGO_INVERTED

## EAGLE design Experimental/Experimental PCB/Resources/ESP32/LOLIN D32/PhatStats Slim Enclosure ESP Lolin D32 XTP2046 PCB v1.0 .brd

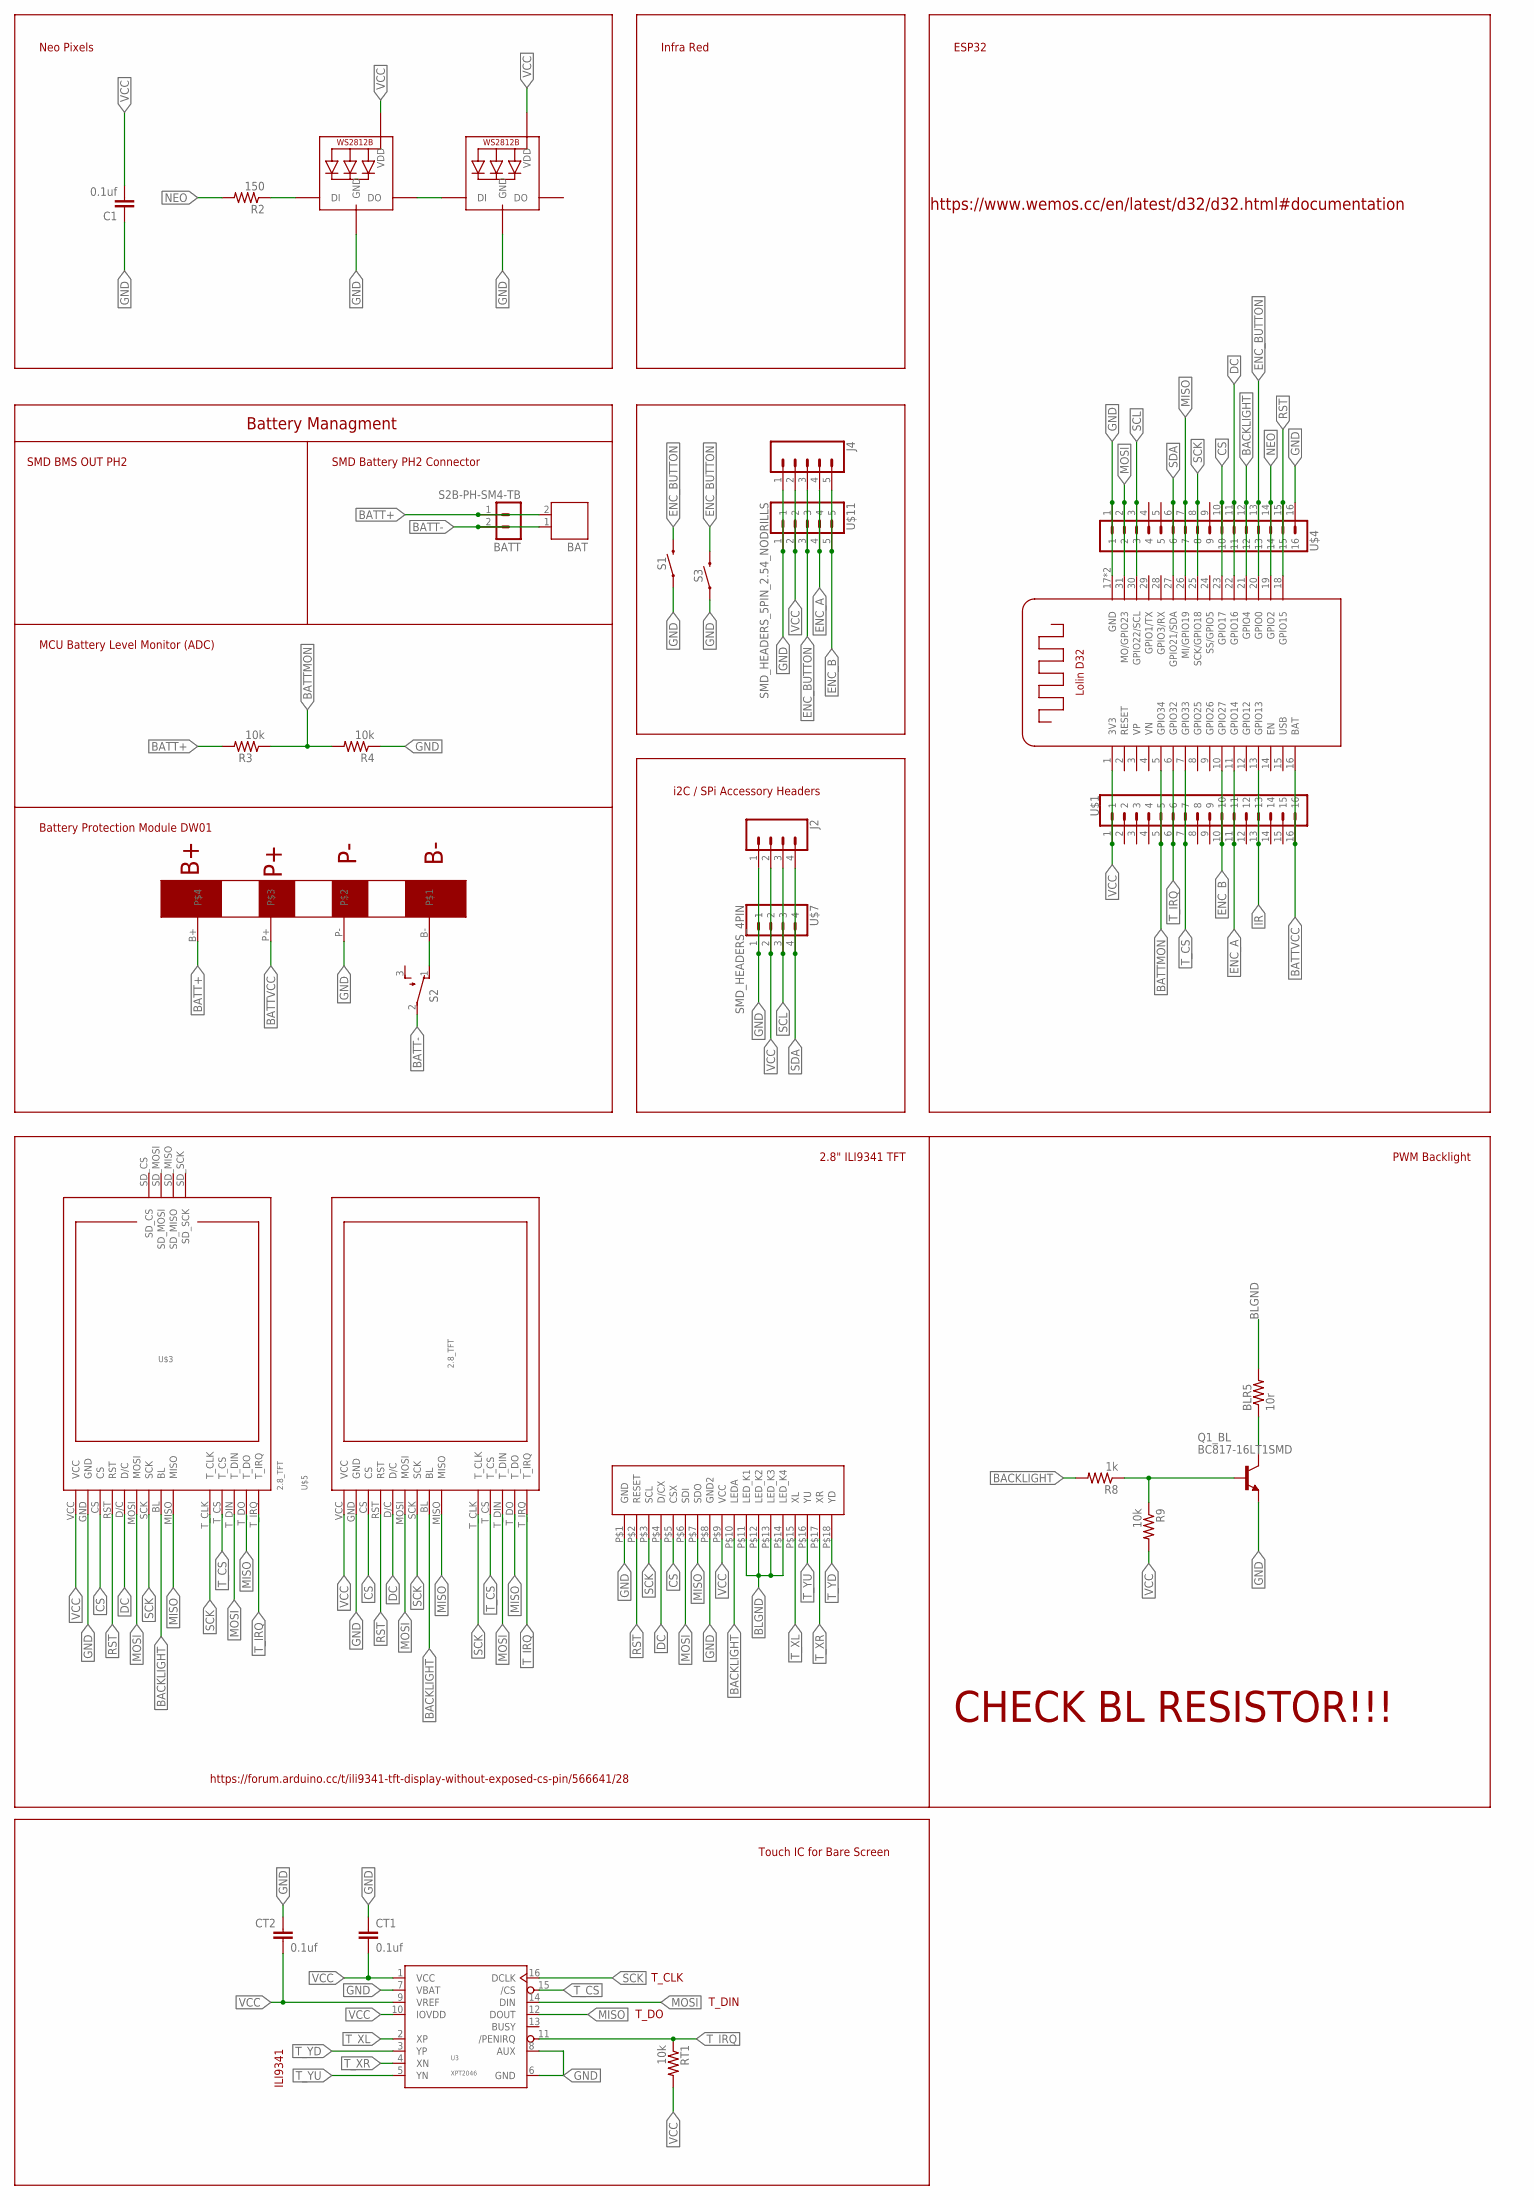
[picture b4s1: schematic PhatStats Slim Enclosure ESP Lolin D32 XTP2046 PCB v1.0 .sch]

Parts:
0: ILI9341-2.8
BAT: JST-PH2
BATT: S2B-PH-SM4-TB
BLR5: 10r; M1206
BMS: DW01BATTERYPROT
C1: 0.1uf; C1206
CT1, CT2: 0.1uf; C1206
J2: CONN_04PTH; 1X04
J4: CONN_05; 1X05
NEO1, NEO2: WS2812B5050; WS2812B
Q1_BL: BC817-16LT1SMD; SOT23-BEC
R2: 150; M1206
R3, R4, R9: 10k; M1206
R8: 1k; M1206
RT1: 10k; M1206
S1: MOMENTARY-SWITCH-SPST-PTH-6.0MM; TACTILE_SWITCH_PTH_6.0MM
S2: SK-12F14(1P2T)0.5A50VDC3MMPITCH
S3: MOMENTARY-SWITCH-SPST-SMD-6.2MM-TALL; TACTILE_SWITCH_SMD_6.2MM_TALL
U3: XPT2046; TSSOP-16
U$1, U$4: SMD_HEADERS_16PIN_2.54_NODRILLSSMD_HEADERS_16PIN; SMD_HEADERS_16PIN
U$2: TML_LOLIND32
U$3, U$5: 2.8_TFT
U$7: SMD_HEADERS_4PIN
U$11: SMD_HEADERS_5PIN_2.54_NODRILLS; SMD_HEADERS_5PIN

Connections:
BACKLIGHT: 0.P$10 (LEDA), R8.2, U$2.21 (GPIO4), U$3.BL, U$4.12, U$5.BL
BATT+: BAT.2, BATT.1, BMS.B+, R3.2
BATT-: BAT.1, BATT.2, S2.2
BATTMON: R3.1, R4.2, U$1.5, U$2.5 (GPIO34)
BATTVCC: BMS.P+, U$1.16, U$2.16 (BAT)
BL: BLR5.1, Q1_BL.C
BLGND: 0.P$11 (LED_K1), 0.P$12 (LED_K2), 0.P$13 (LED_K3), 0.P$14 (LED_K4), BLR5.2
CS: 0.P$5 (CSX), U$2.23 (GPIO17), U$3.CS, U$4.10, U$5.CS
DC: 0.P$4 (D/CX), U$2.22 (GPIO16), U$3.D/C, U$4.11, U$5.D/C
ENC_A: J4.4, U$1.11, U$2.11 (GPIO14), U$11.4
ENC_B: J4.5, U$1.10, U$2.10 (GPIO27), U$11.5
ENC_BUTTON: J4.3, S1.3 (2), S3.B2 (2), U$2.20 (GPIO0), U$4.13, U$11.3
GND: 0.P$1 (GND), 0.P$8 (GND2), BMS.P-, C1.1, CT1.1, CT2.1, J2.1, J4.1, NEO1.3-GND (GND), NEO2.3-GND (GND), Q1_BL.E, R4.1, S1.1, S3.A2 (1), U3.6 (GND), U3.7 (VBAT), U3.8 (AUX), U$2.17 (GND), U$2.32 (GND), U$3.GND, U$4.1, U$4.16, U$5.GND, U$7.1, U$11.1
IR: U$1.13, U$2.13 (GPIO13)
MISO: 0.P$7 (SDO), U3.12 (DOUT), U$2.26 (MI/GPIO19), U$3.MISO, U$3.T_DO, U$4.7, U$5.MISO, U$5.T_DO
MOSI: 0.P$6 (SDI), U3.14 (DIN), U$2.31 (MO/GPIO23), U$3.MOSI, U$3.T_DIN, U$4.2, U$5.MOSI, U$5.T_DIN
unnamed: BMS.B-, S2.1 (O)
unnamed: NEO1.2-DOUT (DO), NEO2.4-DIN (DI)
unnamed: NEO1.4-DIN (DI), R2.1
unnamed: Q1_BL.B, R8.1, R9.1
NEO: R2.2, U$2.19 (GPIO2), U$4.14
RST: 0.P$2 (RESET), U$2.18 (GPIO15), U$3.RST, U$4.15, U$5.RST
SCK: 0.P$3 (SCL), U3.16 (DCLK), U$2.25 (SCK/GPIO18), U$3.SCK, U$3.T_CLK, U$4.8, U$5.SCK, U$5.T_CLK
SCL: J2.3, U$2.30 (GPIO22/SCL), U$4.3, U$7.3
SDA: J2.4, U$2.27 (GPIO21/SDA), U$4.6, U$7.4
T_CS: U3.15 (/CS), U$1.7, U$2.7 (GPIO33), U$3.T_CS, U$5.T_CS
T_IRQ: RT1.1, U3.11 (/PENIRQ), U$1.6, U$2.6 (GPIO32), U$3.T_IRQ, U$5.T_IRQ
T_XL: 0.P$15 (XL), U3.2 (XP)
T_XR: 0.P$17 (XR), U3.4 (XN)
T_YD: 0.P$18 (YD), U3.3 (YP)
T_YU: 0.P$16 (YU), U3.5 (YN)
USB: U$2.15 (USB)
VCC: 0.P$9 (VCC), C1.2, CT1.2, CT2.2, J2.2, J4.2, NEO1.1-VDD (VDD), NEO2.1-VDD (VDD), R9.2, RT1.2, U3.1 (VCC), U3.9 (VREF), U3.10 (IOVDD), U$1.1, U$2.1 (3V3), U$3.VCC, U$5.VCC, U$7.2, U$11.2

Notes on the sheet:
https://forum.arduino.cc/t/ili9341-tft-display-without-exposed-cs-pin/566641/28
SMD BMS OUT PH2
Battery Managment
SMD Battery PH2 Connector
MCU Battery Level Monitor (ADC)
Battery Protection Module DW01
Neo Pixels
Infra Red
i2C / SPi Accessory Headers
ESP32
2.8" ILI9341 TFT
PWM Backlight
CHECK BL RESISTOR!!!
https://www.wemos.cc/en/latest/d32/d32.html#documentation
ILI9341
T_CLK
T_DIN
T_DO
Touch IC for Bare Screen
